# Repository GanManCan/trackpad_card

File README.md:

# MNIST Business Card (Test)

This software is based on the [projet](https://github.com/mr-goldhands/ESP32_Fashion_MNIST), which you can read about i the following medium [article](https://medium.com/@dmytro.korablyov/first-steps-with-esp32-and-tensorflow-lite-for-microcontrollers-c2d8e238accf)

This project makes a PCB "Business Card" with a touchpad input that outputs the numerical ddigit input on the toucpad. using ESP32 microcontroller and tensorflow lite. 

### Hardware

**Microcontroller:**  ESP32.  Specifically, this project uses the ESP32XXXX, which is the single core version with XX MB of flash. 

I choose the ESP32 for two reasons **cost** and **tensorflow lite support**.  The ESP32 is very cheap ,$1.60 in low quanities,  and has numberous tensorflow lite examples that made it easy to learn. 
 
The most signficant drawback of the ESP32 is the power draw, esecially when trying to power the card using a coin cell.  Understandably, when operating at 160 MHz the draws around XX ma.  The ESP32 also has low power and ultra-low power (ULP) mode, which draw XX ma and XX ma, respectivly.  While the ESP32 could techinally commuicate with the I2C touchpad controller in  ULP mode, this would require writing a pretty extivsive program in assembly that is more work than I wanted to take on for this project.  As diiscussed int eh software section, this results in operating almost contiously in the full power mode.

**Touchpad Controller:**

** Schematic ** 

### ESP32 Software.

As mentioned above this project is based on [ESP32_Fashion_MNIST'](https://github.com/mr-goldhands/ESP32_Fashion_MNIST) and [tensorflow lite examples](https://www.tensorflow.org/lite/microcontrollers). 

## Python

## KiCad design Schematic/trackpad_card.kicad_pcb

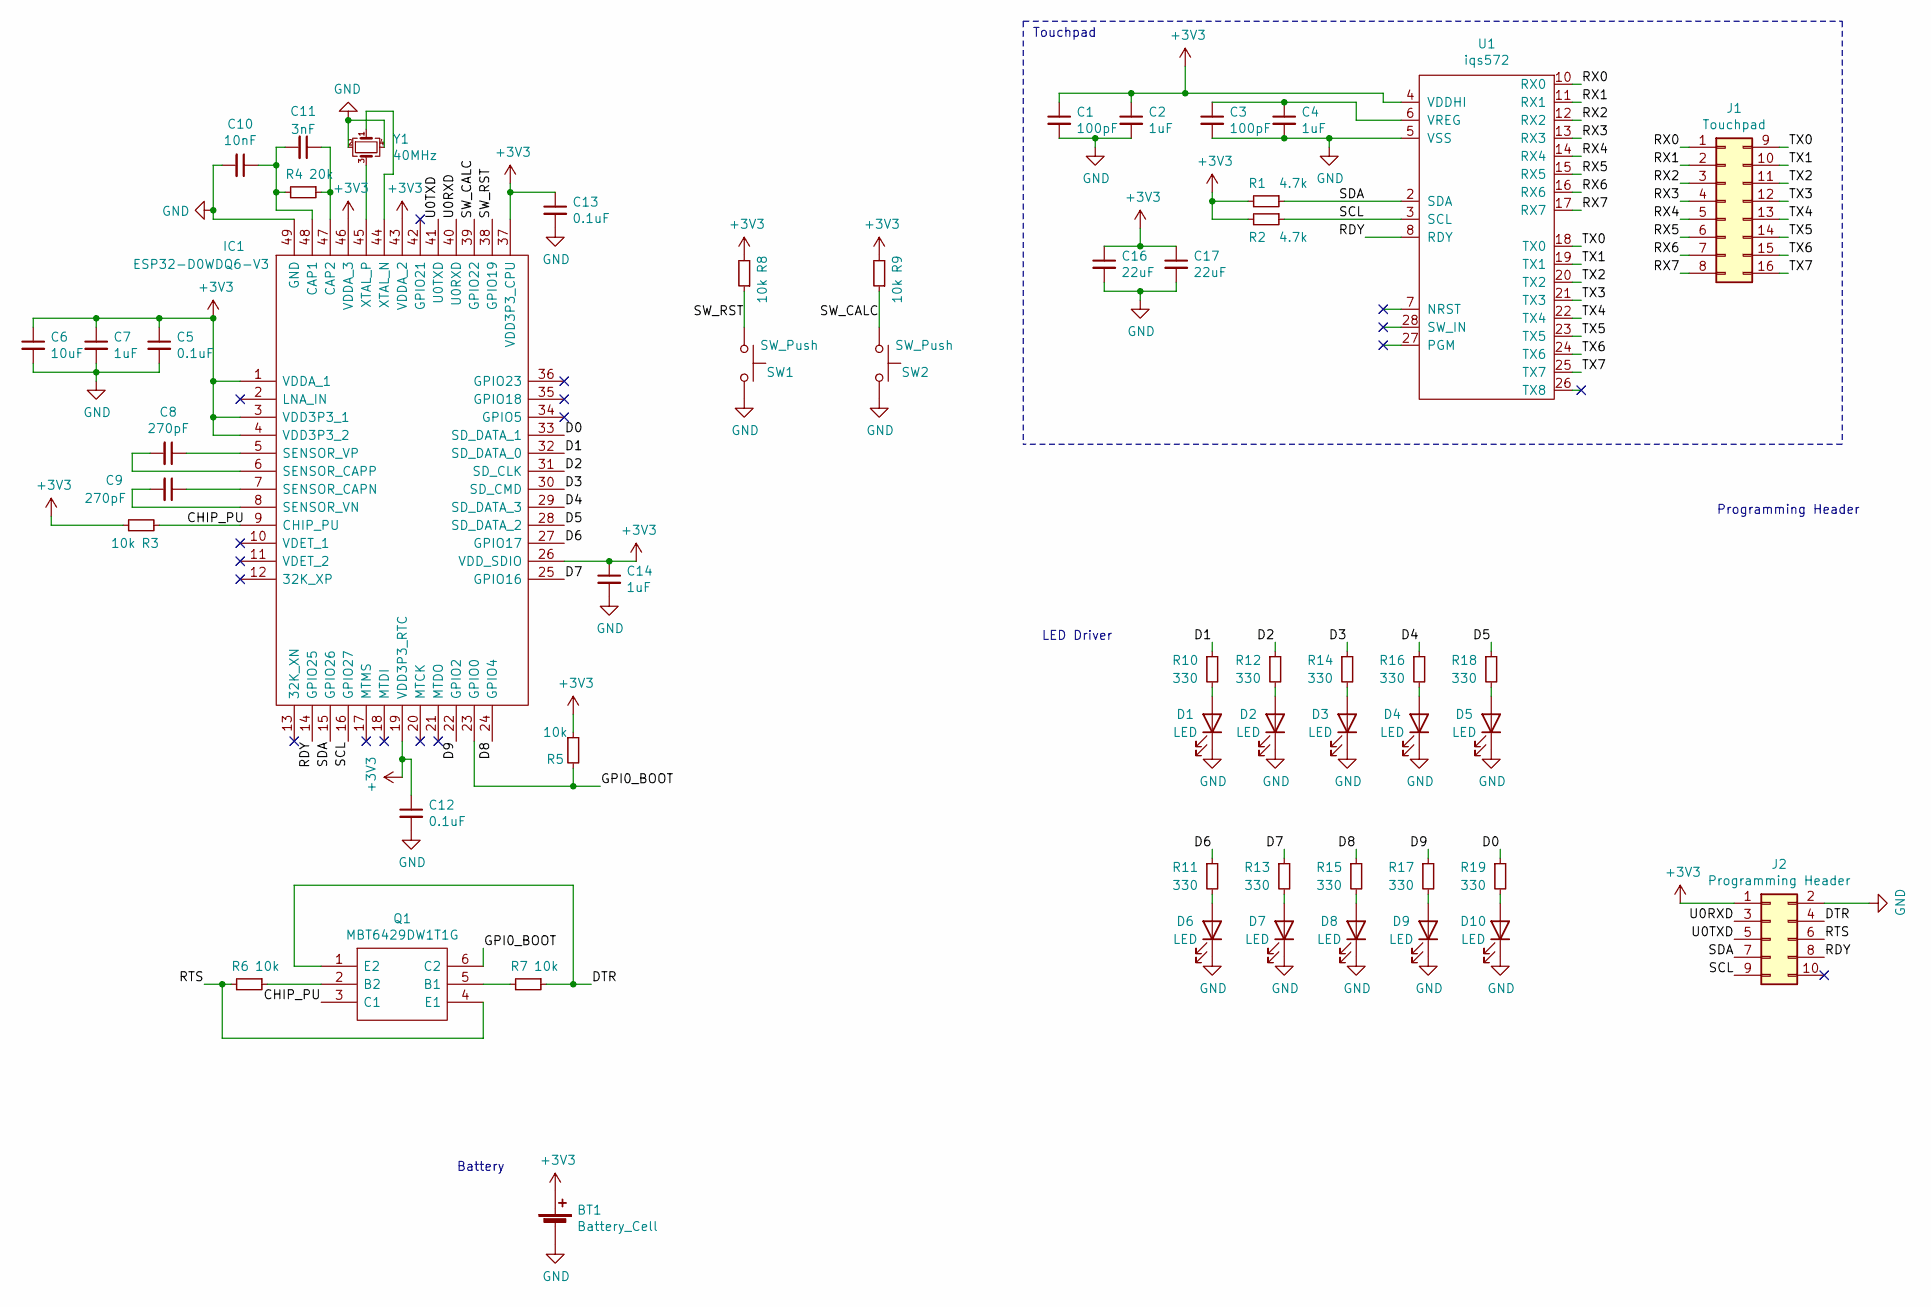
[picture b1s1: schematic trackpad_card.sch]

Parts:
BT1: Battery_Cell; BatteryHolder_Keystone_3034_1x20mm
C1, C3: 100pF; C_0402_1005Metric
C2, C4, C7, C14: 1uF; C_0402_1005Metric
C5, C12, C13: 0.1uF; C_0402_1005Metric
C6: 10uF; C_0402_1005Metric
C8, C9: 270pF; C_0402_1005Metric
C10: 10nF; C_0402_1005Metric
C11: 3nF; C_0402_1005Metric
C16, C17: 22uF; C_0805_2012Metric
D1, D2, D3, D4, D5, D6, D7, D8, D9, D10: LED; LED_0603_1608Metric
IC1: ESP32-D0WDQ6-V3; QFN40P600X600X90-49N-D_vias; Mouser Part Number 356-ESP32-D0WDQ6-V3
J1: Touchpad; trackpad_rect
J2: Programming Header; PinHeader_2x05_P2.54mm_Vertical_SMD
Q1: MBT6429DW1T1G; SOT65P210X110-6N; Mouser Part Number 863-MBT3946DW1T1G
R1, R2: 4.7k; R_0402_1005Metric
R3, R5, R6, R7, R8, R9: 10k; R_0402_1005Metric
R4: 20k; R_0402_1005Metric
R10, R11, R12, R13, R14, R15, R16, R17, R18, R19: 330; R_0402_1005Metric
SW1, SW2: SW_Push; SW_pts526_1.5mm
U1: iqs572; QFN-28_4x4mm_P0.5mm
Y1: 40MHz; Oscillator_SMD_suntsu_ASCO-4Pin_1.6x1.2mm

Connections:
+3V3: BT1.1 (+), C1.1, C2.1, C5.1, C6.1, C7.1, C12.1, C13.1, C14.1, C16.1, C17.1, IC1.1 (VDDA_1), IC1.3 (VDD3P3_1), IC1.4 (VDD3P3_2), IC1.19 (VDD3P3_RTC), IC1.26 (VDD_SDIO), IC1.37 (VDD3P3_CPU), IC1.43 (VDDA_2), IC1.46 (VDDA_3), J2.1, R1.2, R2.2, R3.1, R5.1, R8.2, R9.2, U1.4 (VDDHI)
/CHIP_PU: IC1.9 (CHIP_PU), Q1.3 (C1), R3.2
/D0: IC1.33 (SD_DATA_1), R19.1
/D1: IC1.32 (SD_DATA_0), R10.1
/D2: IC1.31 (SD_CLK), R12.1
/D3: IC1.30 (SD_CMD), R14.1
/D4: IC1.29 (SD_DATA_3), R16.1
/D5: IC1.28 (SD_DATA_2), R18.1
/D6: IC1.27 (GPIO17), R11.1
/D7: IC1.25 (GPIO16), R13.1
/D8: IC1.24 (GPIO4), R15.1
/D9: IC1.22 (GPIO2), R17.1
/DTR: J2.4, Q1.1 (E2), R7.1
/GPI0_BOOT: IC1.23 (GPIO0), Q1.6 (C2), R5.2
/NRST: U1.7 (NRST)
/PGM: U1.27 (PGM)
/RDY: IC1.14 (GPIO25), J2.8, U1.8 (RDY)
/RTS: J2.6, Q1.4 (E1), R6.2
/RX0: J1.1, U1.10 (RX0)
/RX1: J1.2, U1.11 (RX1)
/RX2: J1.3, U1.12 (RX2)
/RX3: J1.4, U1.13 (RX3)
/RX4: J1.5, U1.14 (RX4)
/RX5: J1.6, U1.15 (RX5)
/RX6: J1.7, U1.16 (RX6)
/RX7: J1.8, U1.17 (RX7)
/SCL: IC1.16 (GPIO27), J2.9, R2.1, U1.3 (SCL)
/SDA: IC1.15 (GPIO26), J2.7, R1.1, U1.2 (SDA)
/SW_CALC: IC1.39 (GPIO22), R9.1, SW2.1
/SW_IN: U1.28 (SW_IN)
/SW_RST: IC1.38 (GPIO19), R8.1, SW1.1
/TX0: J1.9, U1.18 (TX0)
/TX1: J1.10, U1.19 (TX1)
/TX2: J1.11, U1.20 (TX2)
/TX3: J1.12, U1.21 (TX3)
/TX4: J1.13, U1.22 (TX4)
/TX5: J1.14, U1.23 (TX5)
/TX6: J1.15, U1.24 (TX6)
/TX7: J1.16, U1.25 (TX7)
/TX8: U1.26 (TX8)
/U0RXD: IC1.40 (U0RXD), J2.3
/U0TXD: IC1.41 (U0TXD), J2.5
GND: BT1.2 (-), C1.2, C2.2, C3.2, C4.2, C5.2, C6.2, C7.2, C10.2, C12.2, C13.2, C14.2, C16.2, C17.2, D1.1 (K), D2.1 (K), D3.1 (K), D4.1 (K), D5.1 (K), D6.1 (K), D7.1 (K), D8.1 (K), D9.1 (K), D10.1 (K), IC1.49 (GND), J2.2, SW1.2, SW2.2, U1.5 (VSS), Y1.2, Y1.4
unnamed: C3.1, C4.1, U1.6 (VREG)
unnamed: C8.1, IC1.5 (SENSOR_VP)
unnamed: C8.2, IC1.6 (SENSOR_CAPP)
unnamed: C9.1, IC1.7 (SENSOR_CAPN)
unnamed: C9.2, IC1.8 (SENSOR_VN)
unnamed: C10.1, C11.2, IC1.48 (CAP1), R4.2
unnamed: C11.1, IC1.47 (CAP2), R4.1
unnamed: D1.2 (A), R10.2
unnamed: D2.2 (A), R12.2
unnamed: D3.2 (A), R14.2
unnamed: D4.2 (A), R16.2
unnamed: D5.2 (A), R18.2
unnamed: D6.2 (A), R11.2
unnamed: D7.2 (A), R13.2
unnamed: D8.2 (A), R15.2
unnamed: D9.2 (A), R17.2
unnamed: D10.2 (A), R19.2
unnamed: IC1.44 (XTAL_N), Y1.1
unnamed: IC1.45 (XTAL_P), Y1.3
unnamed: Q1.2 (B2), R6.1
unnamed: Q1.5 (B1), R7.2

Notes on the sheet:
Touchpad
LED Driver
Battery
Programming Header

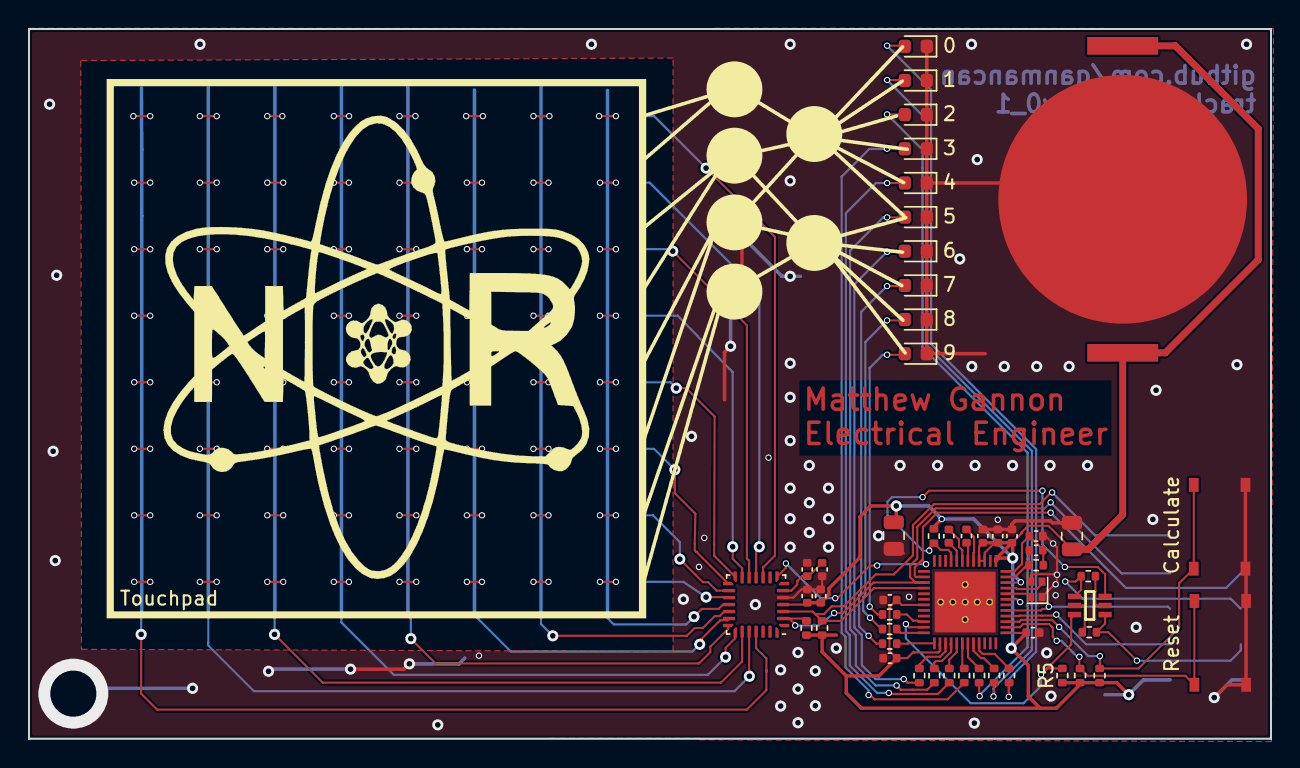
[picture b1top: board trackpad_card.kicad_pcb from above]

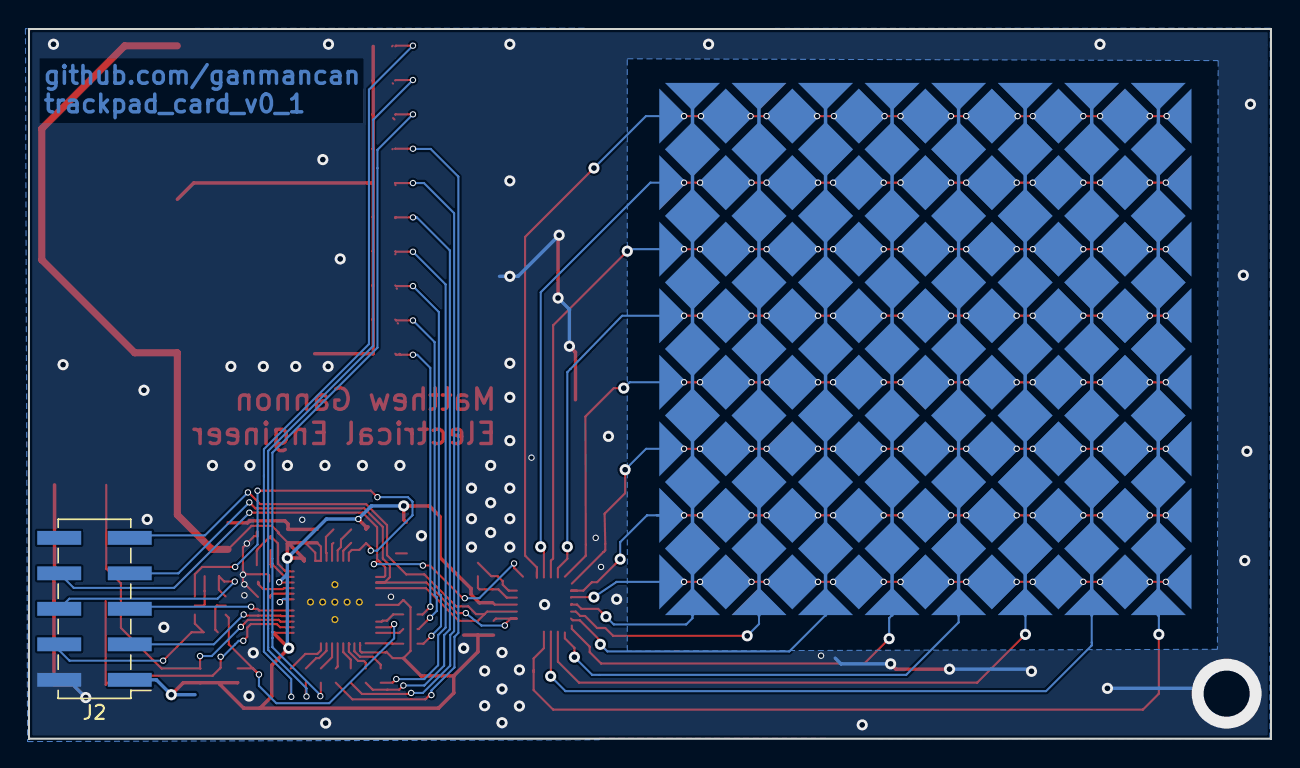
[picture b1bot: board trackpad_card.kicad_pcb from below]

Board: 2 copper layers, 88.9 x 50.8 mm, 54 parts (2 on the bottom side), 60 nets.

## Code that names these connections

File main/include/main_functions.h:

/* Copyright 2019 The TensorFlow Authors. All Rights Reserved.

Licensed under the Apache License, Version 2.0 (the "License");
you may not use this file except in compliance with the License.
You may obtain a copy of the License at

    http://www.apache.org/licenses/LICENSE-2.0

Unless required by applicable law or agreed to in writing, software
distributed under the License is distributed on an "AS IS" BASIS,
WITHOUT WARRANTIES OR CONDITIONS OF ANY KIND, either express or implied.
See the License for the specific language governing permissions and
limitations under the License.
==============================================================================*/

#include "esp_system.h"
#include "driver/uart.h"
#include "driver/gpio.h"
#include "driver/i2c.h"
#include <stdio.h>
#include <stdint.h>

#include "tensorflow/lite/c/common.h"

#define UART_NUMBER (UART_NUM_0)
#define TXD_PIN (GPIO_NUM_1) //(U0TXD)
#define RXD_PIN (GPIO_NUM_3) //(U0RXD)
#define RX_BUF_SIZE 1024

// Button Inputs
#define CALC_PIN  (GPIO_NUM_0)   // Calculate GPIO pin
#define RST_PIN   (GPIO_NUM_19)  // Rst GPIO Pin


//I2C Defines
#define IQS572_I2C_R_ADDR 0xe9
#define IQS572_I2C_W_ADDR 0xe8
#define IQS572_RDY (GPIO_NUM_25)     // gpio number for IQS527 RDY signal

#define SAMPLE_PERIOD_MS		200

#define I2C_SCL_IO				27	               /*!< gpio number for I2C master clock */
#define I2C_SDA_IO				26	               /*!< gpio number for I2C master data  */
#define I2C_FREQ_HZ				100000           /*!< I2C master clock frequency */
#define I2C_PORT_NUM			I2C_NUM_1        /*!< I2C port number for master dev */
#define I2C_TX_BUF_DISABLE  	0                /*!< I2C master do not need buffer */
#define I2C_RX_BUF_DISABLE  	0                /*!< I2C master do not need buffer */

// I2C common protocol defines
#define WRITE_BIT                          I2C_MASTER_WRITE /*!< I2C master write */
#define READ_BIT                           I2C_MASTER_READ  /*!< I2C master read */
#define ACK_CHECK_EN                       0x1              /*!< I2C master will check ack from slave*/
#define ACK_CHECK_DIS                      0x0              /*!< I2C master will not check ack from slave */
#define ACK_VAL                            0x0              /*!< I2C ack value */
#define NACK_VAL                           0x1              /*!< I2C nack value */

void initUart(uart_port_t uart_num);
void readUartBytes(float *data, int imageSize);
int sendData(const char *data);
void normalizeImageData(float *data, int imageSize);
void sendBackPredictions(TfLiteTensor *output);
void zero_input(float *data, int imageSize);
void set_input(float *tf_data, uint8_t *pad_data, int imageSize);
void initI2C();
extern "C" {esp_err_t i2c_master_read_slave_reg(i2c_port_t i2c_num, uint8_t i2c_addr, uint8_t i2c_reg, uint8_t* data_rd, size_t size);}
extern "C" {esp_err_t rdIQS572(uint8_t reg, uint8_t *pdata, uint8_t count);}

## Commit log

2021-01-16 Inital
2021-01-17 test
2021-01-17 remove nested git
2021-01-17 remove submodule
2021-01-17 remove unused file
2021-01-17 test add
2021-01-17 Readme Rev
